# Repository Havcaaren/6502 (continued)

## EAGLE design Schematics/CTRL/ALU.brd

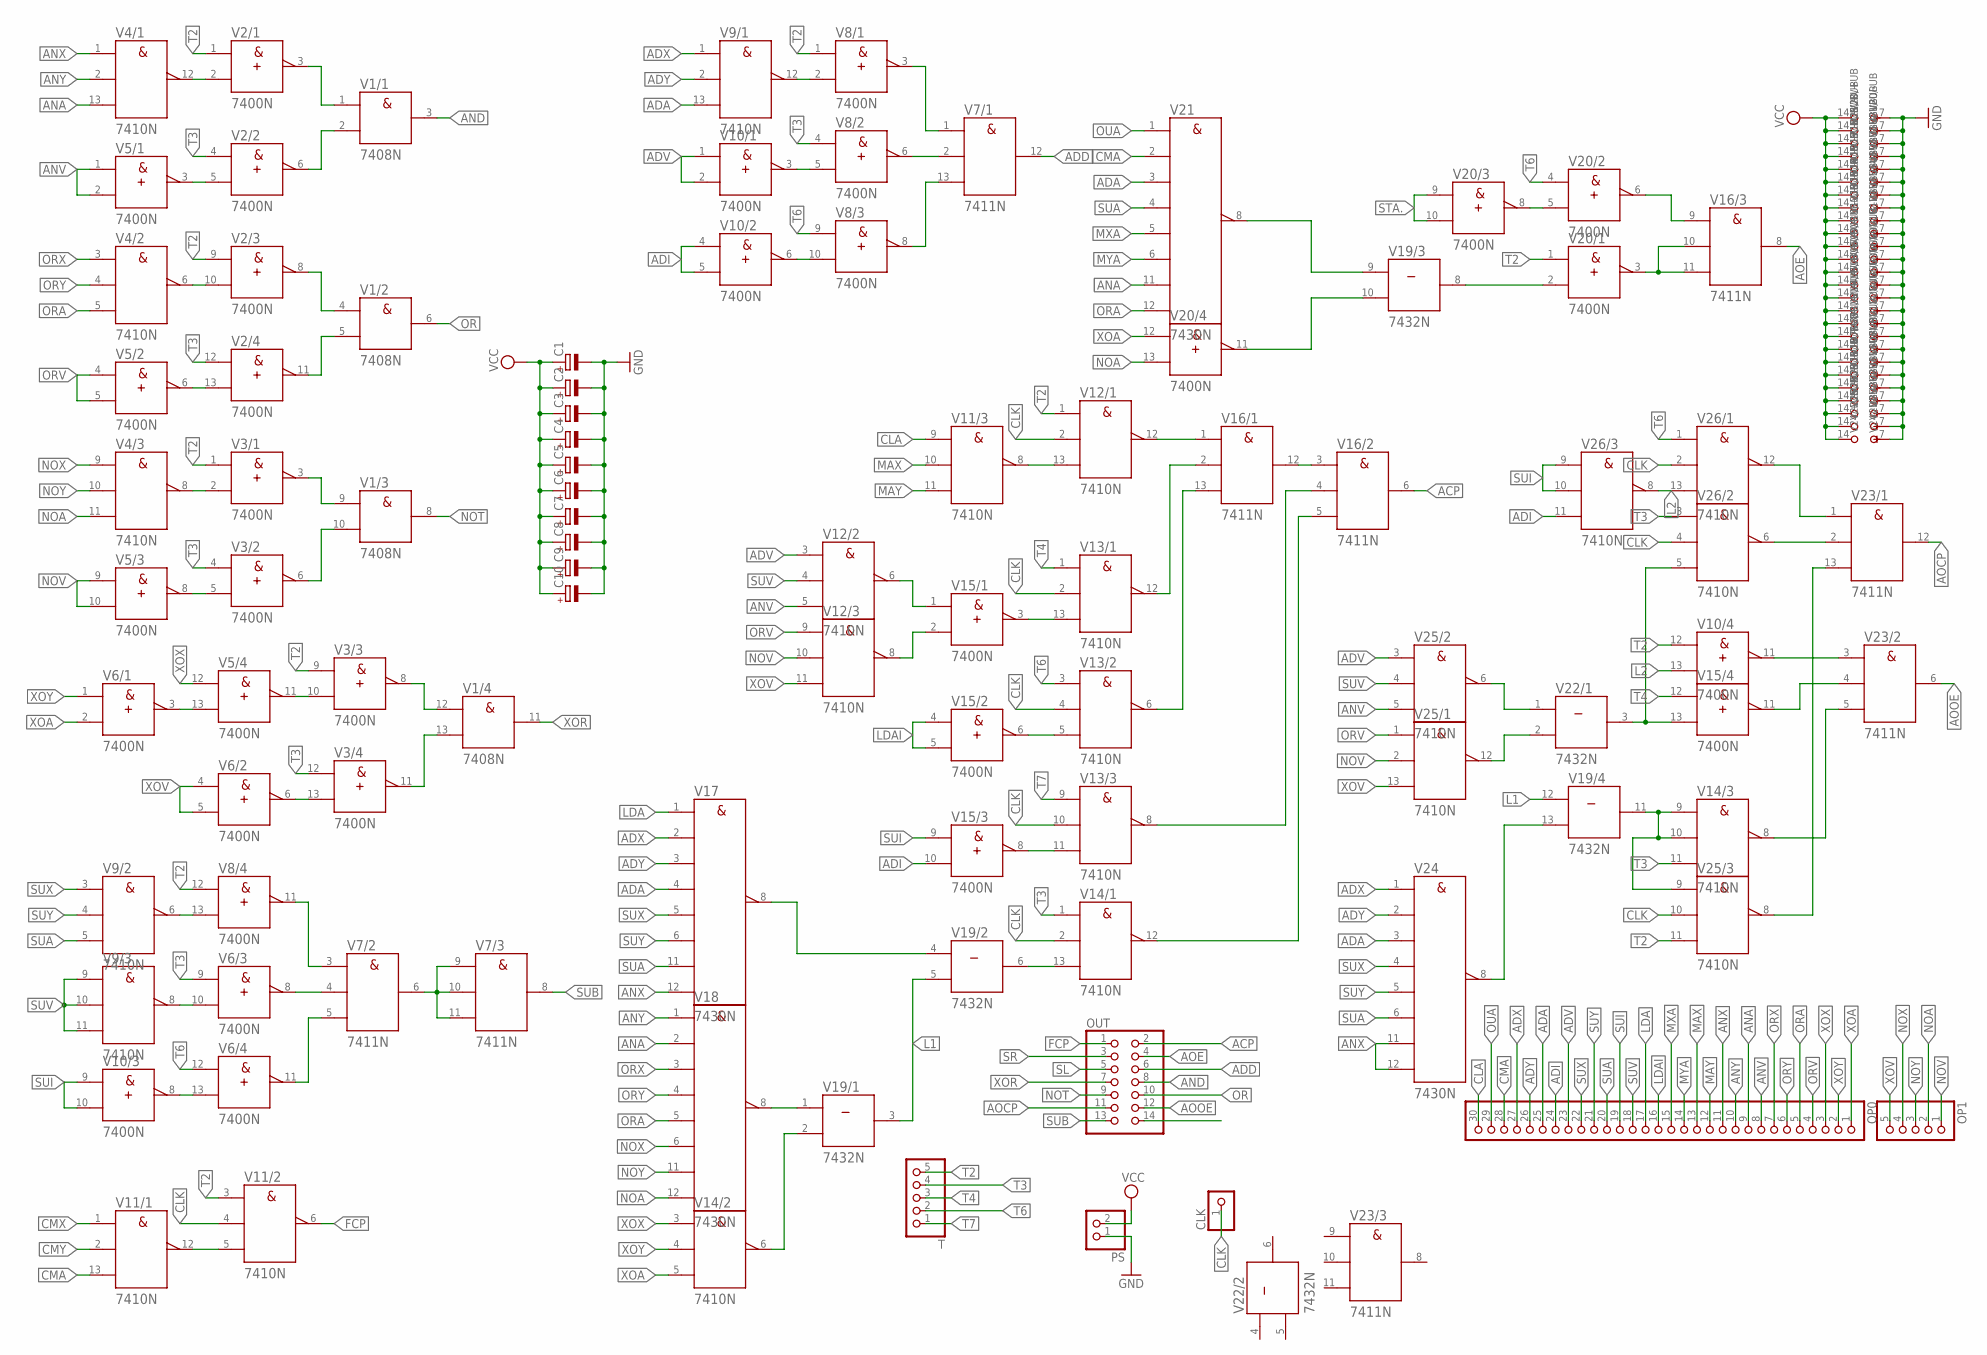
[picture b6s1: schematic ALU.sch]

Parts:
C1, C2, C3, C4, C5, C6, C7, C8, C9, C10: CPOL-EUE2.5-6; E2,5-6
CLK: PINHD-1X1; 1X01
OP0: PINHD-1X30; 1X30
OP1: PINHD-1X5; 1X05
OUT: PINHD-2X7; 2X07
PS: PINHD-1X2; 1X02
T: PINHD-1X5; 1X05
V1: 7408N; DIL14
V2, V3, V5, V6, V8, V10, V15, V20: 7400N; DIL14
V4, V9, V11, V12, V13, V14, V25, V26: 7410N; DIL14
V7, V16, V23: 7411N; DIL14
V17, V18, V21, V24: 7430N; DIL14
V19, V22: 7432N; DIL14

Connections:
ACP: OUT.2, V16.6 (Y)
ADA: OP0.25, V9.13 (C), V17.4 (D), V21.3 (C), V24.3 (C)
ADD: OUT.6, V7.12 (Y)
ADI: OP0.24, V10.4 (A), V10.5 (B), V15.10 (B), V26.11 (C)
ADV: OP0.23, V10.1 (A), V10.2 (B), V12.3 (A), V25.3 (A)
ADX: OP0.27, V9.1 (A), V17.2 (B), V24.1 (A)
ADY: OP0.26, V9.2 (B), V17.3 (C), V24.2 (B)
ANA: OP0.9, V4.13 (C), V18.2 (B), V21.11 (G)
AND: OUT.8, V1.3 (Y)
ANV: OP0.8, V5.1 (A), V5.2 (B), V12.5 (C), V25.5 (C)
ANX: OP0.11, V4.1 (A), V17.12 (H), V24.11 (G), V24.12 (H)
ANY: OP0.10, V4.2 (B), V18.1 (A)
AOCP: OUT.11, V23.12 (Y)
AOE: OUT.4, V16.8 (Y)
AOOE: OUT.12, V23.6 (Y)
CLA: OP0.30, V11.9 (A)
CLK: CLK.1, V11.4 (B), V12.2 (B), V13.2 (B), V13.4 (B), V13.10 (B), V14.2 (B), V25.10 (B), V26.2 (B), V26.4 (B)
CMA: OP0.28, V11.13 (C), V21.2 (B)
CMX: V11.1 (A)
CMY: V11.2 (B)
FCP: OUT.1, V11.6 (Y)
GND: C1.-, C2.-, C3.-, C4.-, C5.-, C6.-, C7.-, C8.-, C9.-, C10.-, PS.1, V1.7 (-UB), V2.7 (-UB), V3.7 (-UB), V4.7 (-UB), V5.7 (-UB), V6.7 (-UB), V7.7 (-UB), V8.7 (-UB), V9.7 (-UB), V10.7 (-UB), V11.7 (-UB), V12.7 (-UB), V13.7 (-UB), V14.7 (-UB), V15.7 (-UB), V16.7 (-UB), V17.7 (-UB), V18.7 (-UB), V19.7 (-UB), V20.7 (-UB), V21.7 (-UB), V22.7 (-UB), V23.7 (-UB), V24.7 (-UB), V25.7 (-UB), V26.7 (-UB)
L1: V19.3 (Y), V19.5 (B), V19.12 (A)
L2: V10.13 (B), V26.8 (Y), V26.13 (C)
LDA: OP0.17, V17.1 (A)
LDAI: OP0.16, V15.4 (A), V15.5 (B)
MAX: OP0.13, V11.10 (B)
MAY: OP0.12, V11.11 (C)
MXA: OP0.15, V21.5 (E)
MYA: OP0.14, V21.6 (F)
unnamed: V1.9 (A), V3.3 (Y)
unnamed: V2.5 (B), V5.3 (Y)
unnamed: V1.10 (B), V3.6 (Y)
unnamed: V1.2 (B), V2.6 (Y)
unnamed: V1.1 (A), V2.3 (Y)
unnamed: V1.12 (A), V3.8 (Y)
unnamed: V2.2 (B), V4.12 (Y)
unnamed: V3.5 (B), V5.8 (Y)
unnamed: V2.10 (B), V4.6 (Y)
unnamed: V1.13 (B), V3.11 (Y)
unnamed: V3.2 (B), V4.8 (Y)
unnamed: V2.13 (B), V5.6 (Y)
unnamed: V1.5 (B), V2.11 (Y)
unnamed: V1.4 (A), V2.8 (Y)
unnamed: V7.2 (B), V8.6 (Y)
unnamed: V5.13 (B), V6.3 (Y)
unnamed: V7.1 (A), V8.3 (Y)
unnamed: V12.6 (Y), V15.1 (A)
unnamed: V3.10 (B), V5.11 (Y)
unnamed: V7.13 (C), V8.8 (Y)
unnamed: V3.13 (B), V6.6 (Y)
unnamed: V12.8 (Y), V15.2 (B)
unnamed: V8.2 (B), V9.12 (Y)
unnamed: V16.3 (A), V16.12 (Y)
unnamed: V8.5 (B), V10.3 (Y)
unnamed: V11.5 (C), V11.12 (Y)
unnamed: V8.10 (B), V10.6 (Y)
unnamed: V18.8 (Y), V19.1 (A)
unnamed: V8.13 (B), V9.6 (Y)
unnamed: V16.10 (B), V16.11 (C), V20.3 (Y)
unnamed: V6.10 (B), V9.8 (Y)
unnamed: V14.6 (Y), V19.2 (B)
unnamed: V6.13 (B), V10.8 (Y)
unnamed: V6.8 (Y), V7.4 (B)
unnamed: V7.3 (A), V8.11 (Y)
unnamed: V6.11 (Y), V7.5 (C)
unnamed: V7.6 (Y), V7.9 (A), V7.10 (B), V7.11 (C)
unnamed: V17.8 (Y), V19.4 (A)
unnamed: V14.13 (C), V19.6 (Y)
unnamed: V13.13 (C), V15.3 (Y)
unnamed: V20.5 (B), V20.8 (Y)
unnamed: V11.8 (Y), V12.13 (C)
unnamed: V19.8 (Y), V20.2 (B)
unnamed: V16.9 (A), V20.6 (Y)
unnamed: V10.11 (Y), V23.3 (A)
unnamed: V19.10 (B), V20.11 (Y)
unnamed: V19.9 (A), V21.8 (Y)
unnamed: V12.12 (Y), V16.1 (A)
unnamed: V13.12 (Y), V16.2 (B)
unnamed: V13.6 (Y), V16.13 (C)
unnamed: V13.8 (Y), V16.4 (B)
unnamed: V14.12 (Y), V16.5 (C)
unnamed: V15.11 (Y), V23.4 (B)
unnamed: V13.5 (C), V15.6 (Y)
unnamed: V13.11 (C), V15.8 (Y)
unnamed: V14.8 (Y), V23.5 (C)
unnamed: V23.2 (B), V26.6 (Y)
unnamed: V23.1 (A), V26.12 (Y)
unnamed: V14.9 (A), V14.10 (B), V19.11 (Y), V25.9 (A)
unnamed: V15.13 (B), V22.3 (Y), V26.5 (C)
unnamed: V23.13 (C), V25.8 (Y)
unnamed: V19.13 (B), V24.8 (Y)
unnamed: V22.2 (B), V25.12 (Y)
unnamed: V22.1 (A), V25.6 (Y)
NOA: OP1.2, V4.11 (C), V18.12 (H), V20.13 (B)
NOT: OUT.9, V1.8 (Y)
NOV: OP1.1, V5.9 (A), V5.10 (B), V12.10 (B), V25.2 (B)
NOX: OP1.4, V4.9 (A), V18.6 (F)
NOY: OP1.3, V4.10 (B), V18.11 (G)
OR: OUT.10, V1.6 (Y)
ORA: OP0.5, V4.5 (C), V18.5 (E), V21.12 (H)
ORV: OP0.4, V5.4 (A), V5.5 (B), V12.9 (A), V25.1 (A)
ORX: OP0.7, V4.3 (A), V18.3 (C)
ORY: OP0.6, V4.4 (B), V18.4 (D)
OUA: OP0.29, V21.1 (A)
SL: OUT.5
SR: OUT.3
STA.: V20.9 (A), V20.10 (B)
SUA: OP0.20, V9.5 (C), V17.11 (G), V21.4 (D), V24.6 (F)
SUB: OUT.13, V7.8 (Y)
SUI: OP0.19, V10.9 (A), V10.10 (B), V15.9 (A), V26.9 (A), V26.10 (B)
SUV: OP0.18, V9.9 (A), V9.10 (B), V9.11 (C), V12.4 (B), V25.4 (B)
SUX: OP0.22, V9.3 (A), V17.5 (E), V24.4 (D)
SUY: OP0.21, V9.4 (B), V17.6 (F), V24.5 (E)
T2: T.5, V2.1 (A), V2.9 (A), V3.1 (A), V3.9 (A), V8.1 (A), V8.12 (A), V10.12 (A), V11.3 (A), V12.1 (A), V20.1 (A), V25.11 (C)
T3: T.4, V2.4 (A), V2.12 (A), V3.4 (A), V3.12 (A), V6.9 (A), V8.4 (A), V14.1 (A), V14.11 (C), V26.3 (A)
T4: T.3, V13.1 (A), V15.12 (A)
T6: T.2, V6.12 (A), V8.9 (A), V13.3 (A), V20.4 (A), V26.1 (A)
T7: T.1, V13.9 (A)
VCC: C1.+, C2.+, C3.+, C4.+, C5.+, C6.+, C7.+, C8.+, C9.+, C10.+, PS.2, V1.14 (+UB), V2.14 (+UB), V3.14 (+UB), V4.14 (+UB), V5.14 (+UB), V6.14 (+UB), V7.14 (+UB), V8.14 (+UB), V9.14 (+UB), V10.14 (+UB), V11.14 (+UB), V12.14 (+UB), V13.14 (+UB), V14.14 (+UB), V15.14 (+UB), V16.14 (+UB), V17.14 (+UB), V18.14 (+UB), V19.14 (+UB), V20.14 (+UB), V21.14 (+UB), V22.14 (+UB), V23.14 (+UB), V24.14 (+UB), V25.14 (+UB), V26.14 (+UB)
XOA: OP0.1, V6.2 (B), V14.5 (C), V20.12 (A)
XOR: OUT.7, V1.11 (Y)
XOV: OP1.5, V6.4 (A), V6.5 (B), V12.11 (C), V25.13 (C)
XOX: OP0.3, V5.12 (A), V14.3 (A)
XOY: OP0.2, V6.1 (A), V14.4 (B)

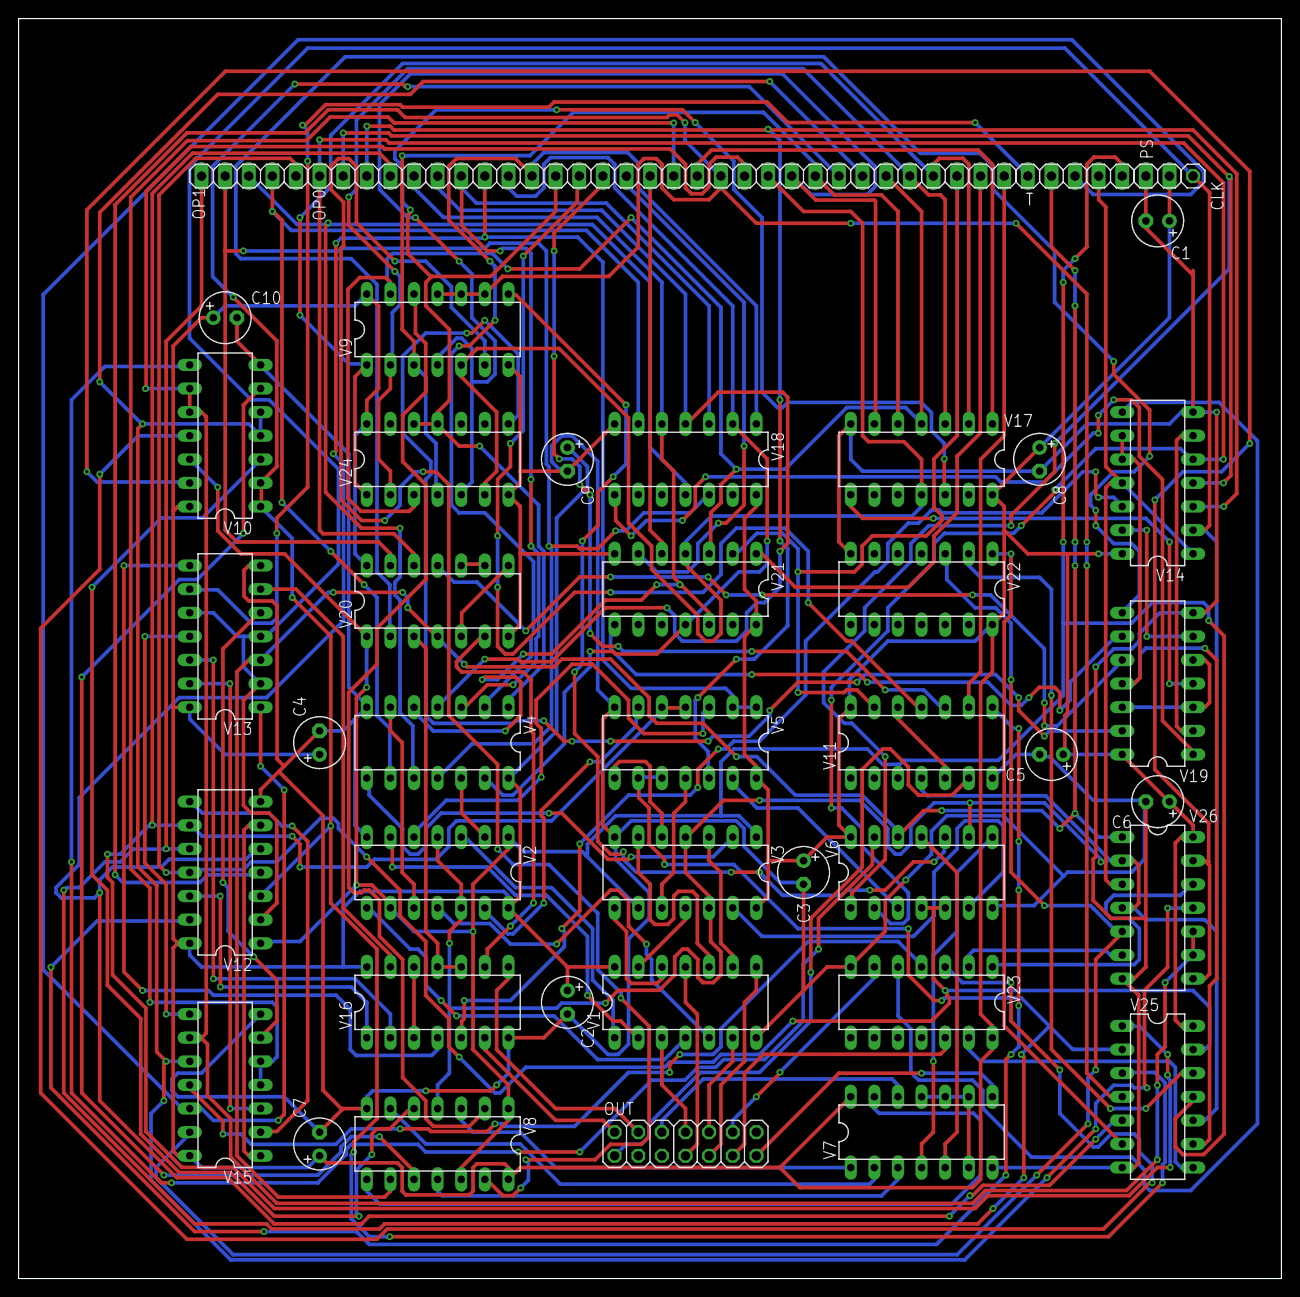
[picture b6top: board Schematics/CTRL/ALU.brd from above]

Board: 2 copper layers, 135.9 x 135.6 mm, 42 parts (0 on the bottom side), 121 nets.
